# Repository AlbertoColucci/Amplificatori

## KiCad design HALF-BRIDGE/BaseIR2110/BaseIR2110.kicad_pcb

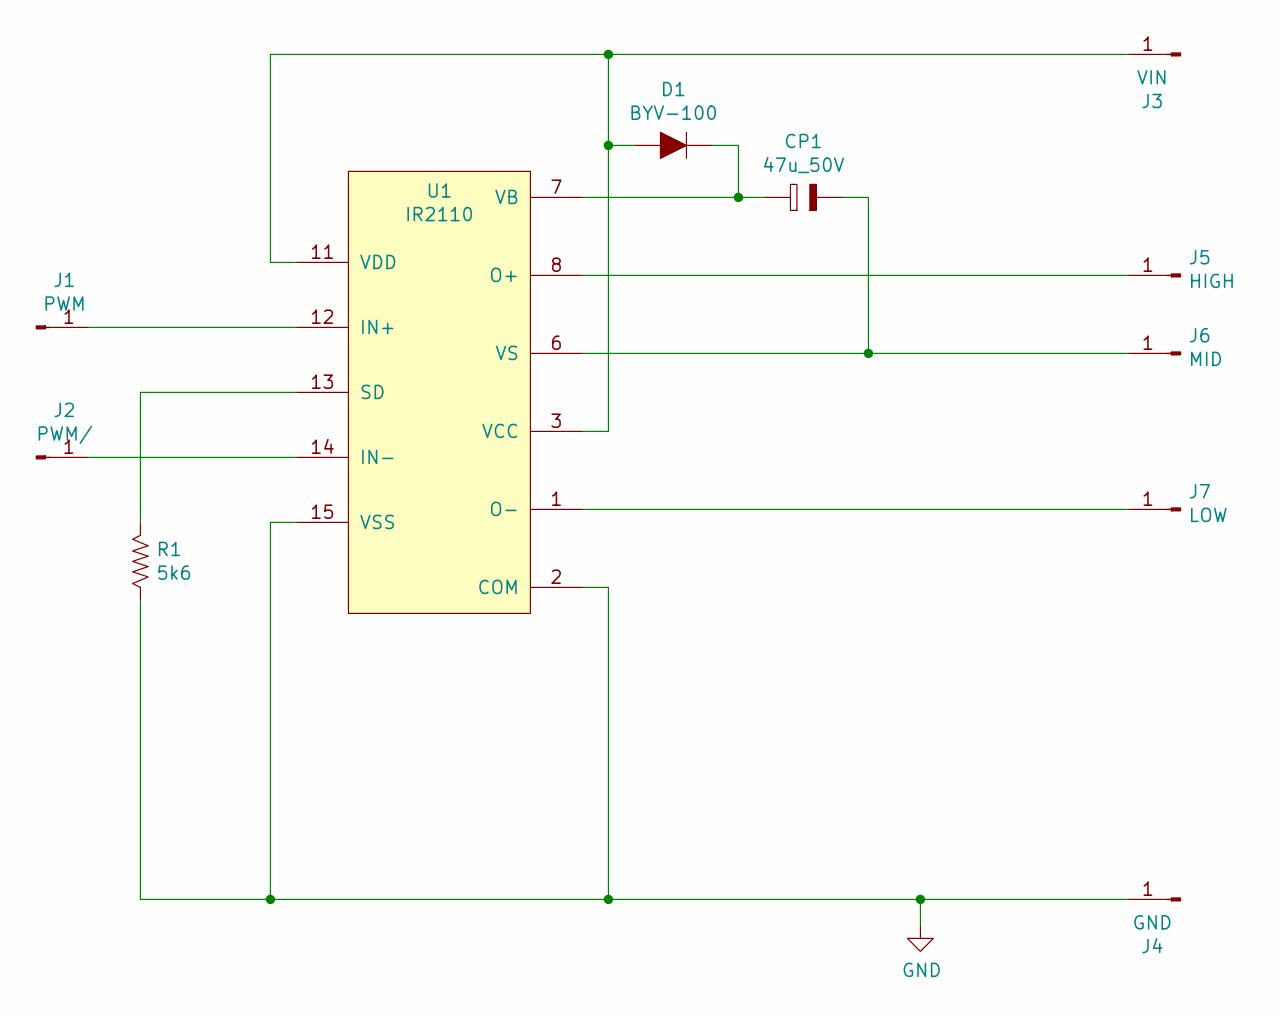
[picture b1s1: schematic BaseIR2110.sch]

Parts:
CP1: 47u_50V; CP_D6.3_P2.54
D1: BYV-100; SOD-64
J1: PWM; 1x1-Pin
J2: PWM/; 1x1-Pin
J3: VIN; 1x1-Pin
J4: GND; 1x1-Pin
J5: HIGH; 1x1-Pin
J6: MID; 1x1-Pin
J7: LOW; 1x1-Pin
R1: 5k6; R_P7.62H
U1: IR2110; SOIC-16W

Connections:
GND: J4.1, R1.2, U1.2 (COM), U1.15 (VSS)
unnamed: CP1.1, J6.1, U1.6 (VS)
unnamed: CP1.2, D1.1 (K), U1.7 (VB)
unnamed: D1.2 (A), J3.1, U1.3 (VCC), U1.11 (VDD)
unnamed: J1.1, U1.12 (IN+)
unnamed: J2.1, U1.14 (IN-)
unnamed: J5.1, U1.8 (O+)
unnamed: J7.1, U1.1 (O-)
unnamed: R1.1, U1.13 (SD)

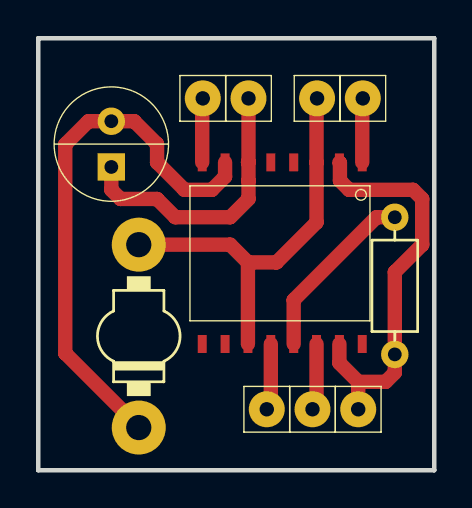
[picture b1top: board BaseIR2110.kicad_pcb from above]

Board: 2 copper layers, 22.0 x 24.0 mm, 11 parts (0 on the bottom side), 9 nets.

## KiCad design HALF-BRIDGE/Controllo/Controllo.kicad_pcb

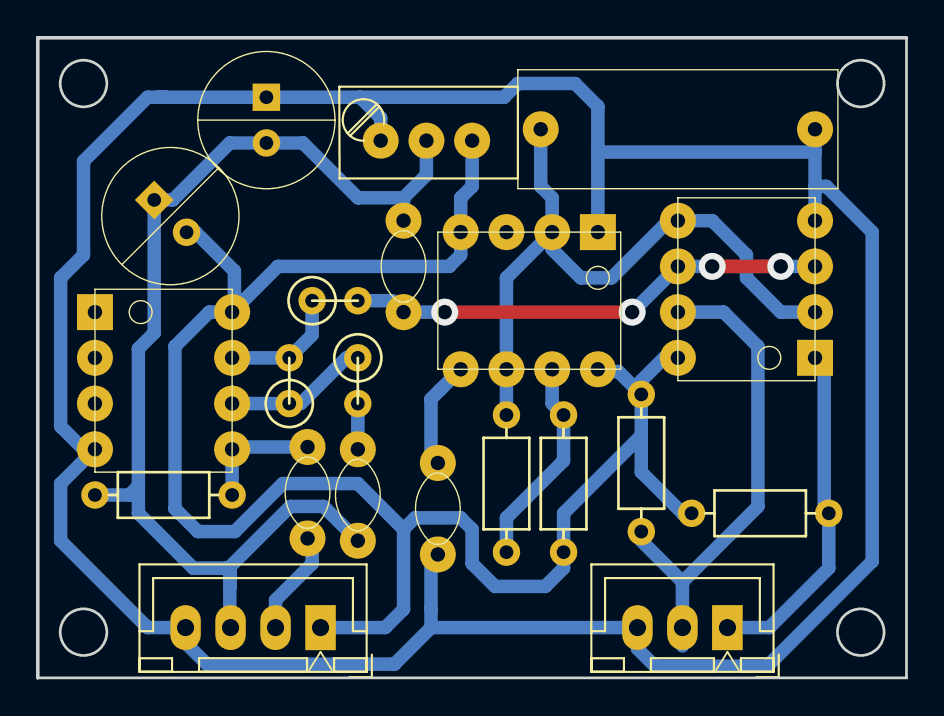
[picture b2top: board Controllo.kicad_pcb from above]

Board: 2 copper layers, 48.3 x 35.6 mm, 21 parts (0 on the bottom side), 14 nets.

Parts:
C1, C3: 1u; C_L5_W2.7_P5.08
C4: 10n; C_L5_W2.7_P5.08
C5: 680p; C_L18_W5.08_P15
C6: 1n; C_L5_W2.7_P5.08
CP1, CP2: 10µ; CP_D7.62_P2.54
J3: PWMOut; 1x03_P2.54
J4: AmpPowerSigIn; 1x04_P2.54
R2: 2.2k; R_P7.62H
R3: 3.3k; R_P2.54V
R4: 36k; R_P2.54V
R5: 680; R_P2.54V
R6: 100; R_P7.62H
R7: 10k; R_P7.62H
R8, R9: 1.5k; R_P7.62H
RV1: 100k; Bourns_3296
U1: LM393; DIP-8
U2: TL072; DIP-8
U3: NE555; DIP-8

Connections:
GND: C5.2, C6.2, CP2.1, J3.3, J4.4, RV1.1, U1.4, U2.4, U3.1
unnamed: C1.1, R2.2, U2.5
unnamed: C1.2, J4.2
unnamed: C3.1, R3.2
unnamed: C3.2, C4.1, CP1.1, CP2.2, J4.3, R2.1, RV1.2
unnamed: C4.2, R5.2, U1.3, U1.6
unnamed: C5.1, R6.2, U1.2, U1.5, U3.2, U3.6
unnamed: C6.1, U3.5
unnamed: J3.1, R8.2, U1.1
unnamed: J3.2, R9.2, U1.7
unnamed: R3.1, R4.1, U2.6
unnamed: R4.2, R5.1, U2.7
unnamed: R6.1, R7.2, U3.7
VCC: CP1.2, J4.1, R7.1, R8.1, R9.1, RV1.3, U1.8, U2.8, U3.4, U3.8

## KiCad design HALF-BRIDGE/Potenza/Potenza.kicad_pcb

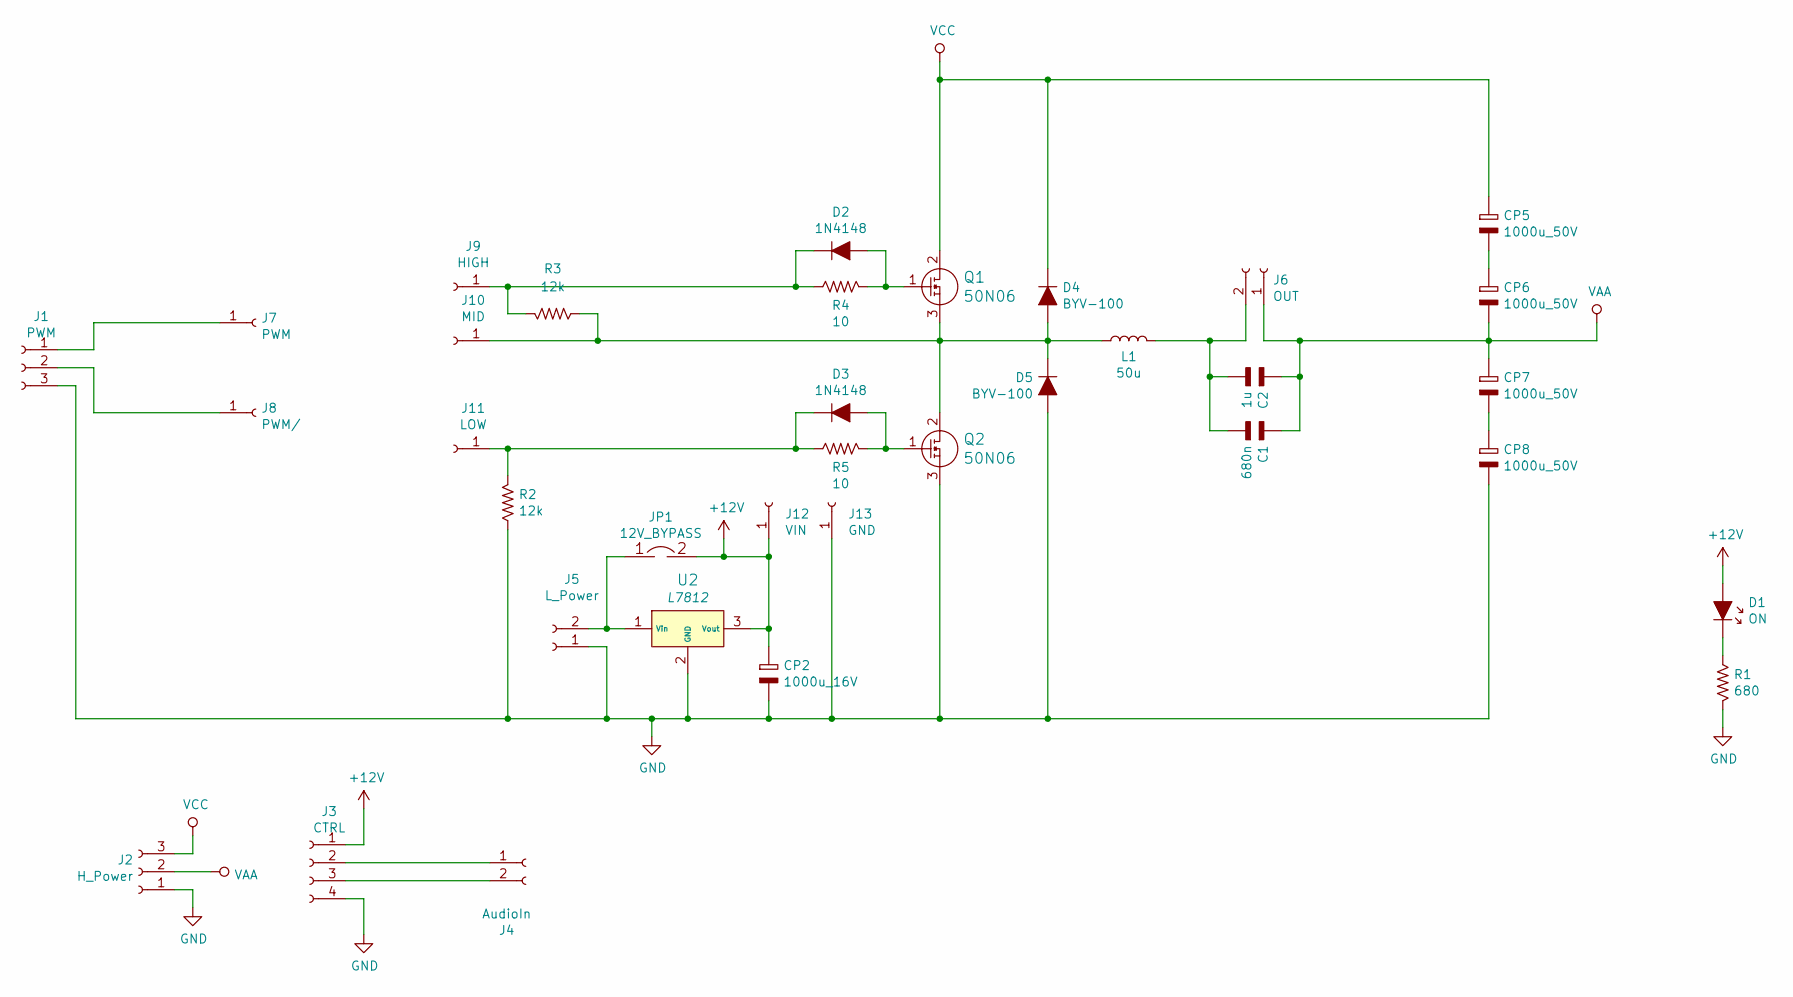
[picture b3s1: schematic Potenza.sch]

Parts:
C1: 680n; C_L23_W6.8_P20
C2: 1u; C_L23_W6.8_P20
CP2: 1000u_16V; CP_D10_P5.08
CP5, CP6, CP7, CP8: 1000u_50V; CP_D13_P5.08
D1: ON; LED_3.0mm
D2, D3: 1N4148; DO-35
D4, D5: BYV-100; SOD-64
J1: PWM; 1x03_P2.54
J2: H_Power; AK300-3
J3: CTRL; 1x04_P2.54
J4: AudioIn; 1x02_P2.54
J5: L_Power; AK300-2
J6: OUT; AK300-2
J7: PWM; 1x1-Pin
J8: PWM/; 1x1-Pin
J9: HIGH; 1x1-Pin
J10: MID; 1x1-Pin
J11: LOW; 1x1-Pin
J12: VIN; 1x1-Pin
J13: GND; 1x1-Pin
JP1: 12V_BYPASS; 1x2-Pin
L1: 50u; T106
Q1, Q2: 50N06; TO-220_3V_FWD
R1: 680; R_P7.62H
R2, R3: 12k; R_P7.62H
R4, R5: 10; R_P7.62H
U2: L7812; TO-220_3H_FWD

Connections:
+12V: CP2.2, D1.1 (A), J3.1, J12.1, JP1.2, U2.3 (Vout)
GND: CP2.1, CP8.1, D5.2 (A), J1.3, J2.1, J3.4, J5.1, J13.1, Q2.3 (S), R1.2, R2.1, U2.2 (GND)
unnamed: C1.2, C2.2, J6.2, L1.2
unnamed: CP5.1, CP6.2
unnamed: CP7.1, CP8.2
unnamed: D1.2 (K), R1.1
unnamed: D2.1 (K), J9.1, R3.2, R4.1
unnamed: D2.2 (A), Q1.1 (G), R4.2
unnamed: D3.1 (K), J11.1, R2.2, R5.1
unnamed: D3.2 (A), Q2.1 (G), R5.2
unnamed: D4.2 (A), D5.1 (K), J10.1, L1.1, Q1.3 (S), Q2.2 (D), R3.1
unnamed: J1.1, J7.1
unnamed: J1.2, J8.1
unnamed: J3.2, J4.1
unnamed: J3.3, J4.2
unnamed: J5.2, JP1.1, U2.1 (Vin)
VAA: C1.1, C2.1, CP6.1, CP7.2, J2.2, J6.1
VCC: CP5.2, D4.1 (K), J2.3, Q1.2 (D)

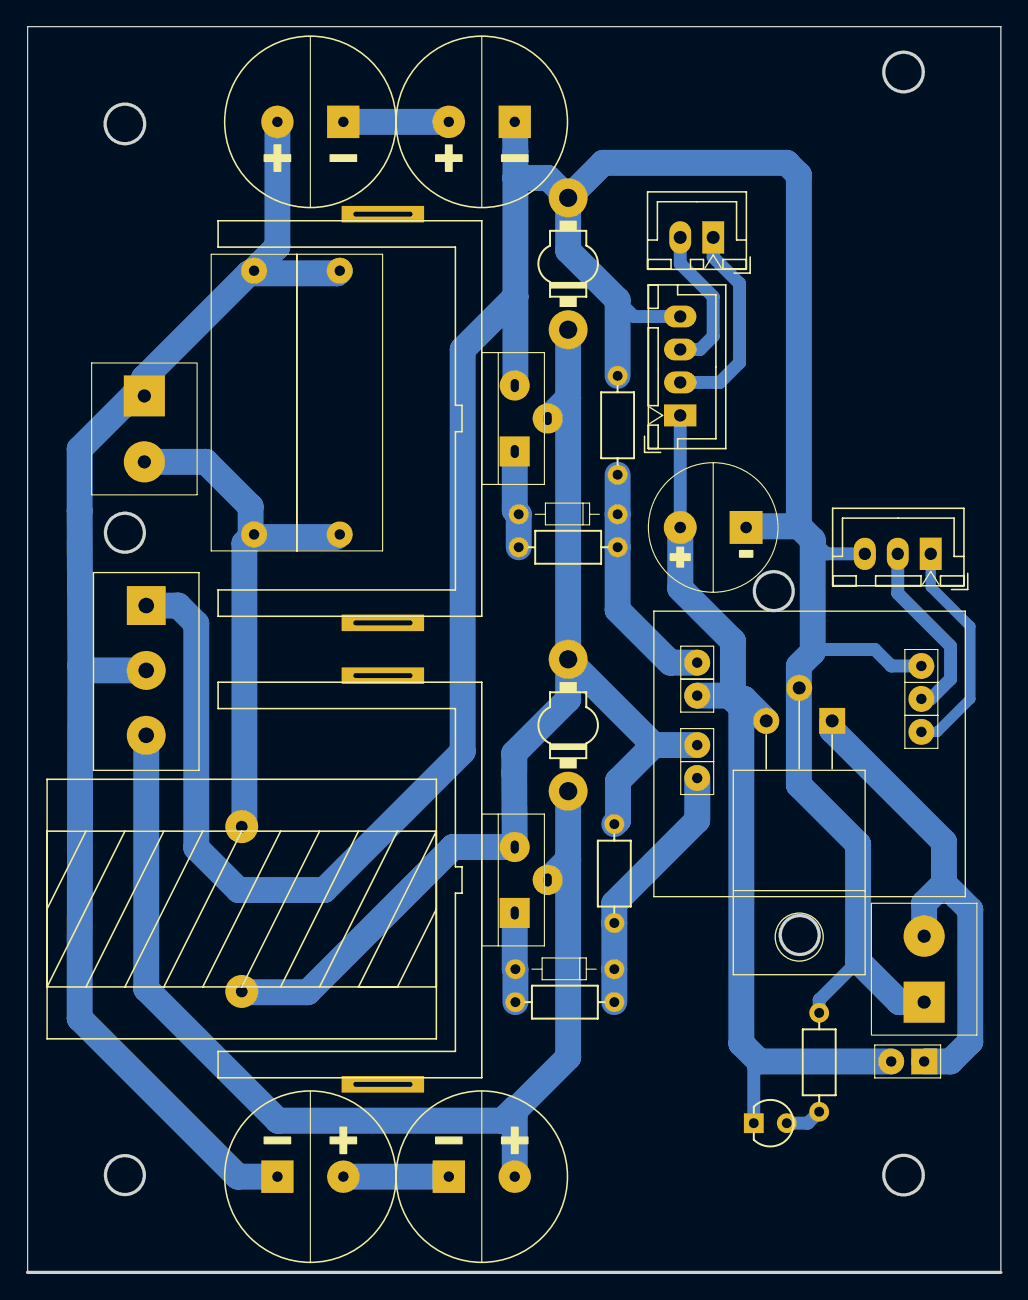
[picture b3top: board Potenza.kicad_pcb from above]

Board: 2 copper layers, 75.0 x 96.0 mm, 35 parts (0 on the bottom side), 18 nets.

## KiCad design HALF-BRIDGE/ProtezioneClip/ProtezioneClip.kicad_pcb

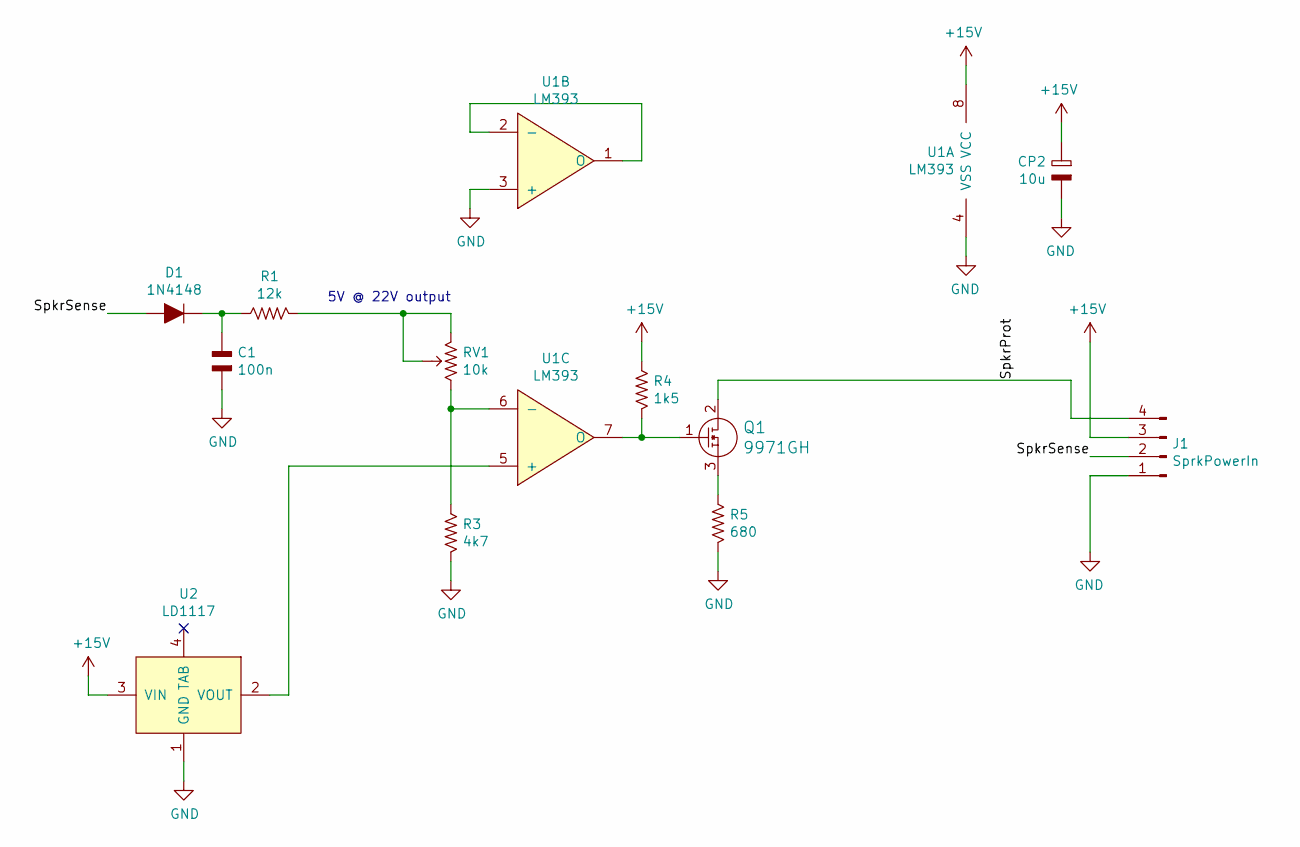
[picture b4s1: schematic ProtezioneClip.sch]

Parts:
C1: 100n; C_L5_W2.7_P5.08
CP2: 10u; CP_D5_P2.54
D1: 1N4148; DO-35
J1: SprkPowerIn; 1x04_P2.54
Q1: 9971GH; TO-252_3_Tab2
R1: 12k; R_P2.54V
R3: 4k7; R_P7.62H
R4: 1k5; R_P2.54V
R5: 680; R_P7.62H
RV1: 10k; Bourns_3296
U1: LM393; SOIC-8
U2: LD1117; SOT-223

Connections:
+15V: CP2.2, J1.3, R4.1, U1.8 (VCC), U2.3 (VIN)
/SpkrProt: J1.4, Q1.2 (D)
/SpkrSense: D1.2 (A), J1.2
GND: C1.1, CP2.1, J1.1, R3.2, R5.2, U1.3 (+), U1.4 (VSS), U2.1 (GND)
unnamed: C1.2, D1.1 (K), R1.1
unnamed: Q1.1 (G), R4.2, U1.7 (O)
unnamed: Q1.3 (S), R5.1
unnamed: R1.2, RV1.2, RV1.3
unnamed: R3.1, RV1.1, U1.6 (-)
unnamed: U1.1 (O), U1.2 (-)
unnamed: U1.5 (+), U2.2 (VOUT)

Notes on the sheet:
5V @ 22V output

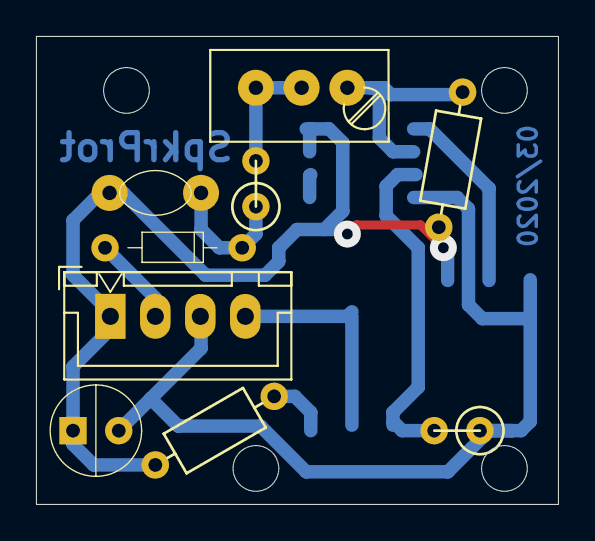
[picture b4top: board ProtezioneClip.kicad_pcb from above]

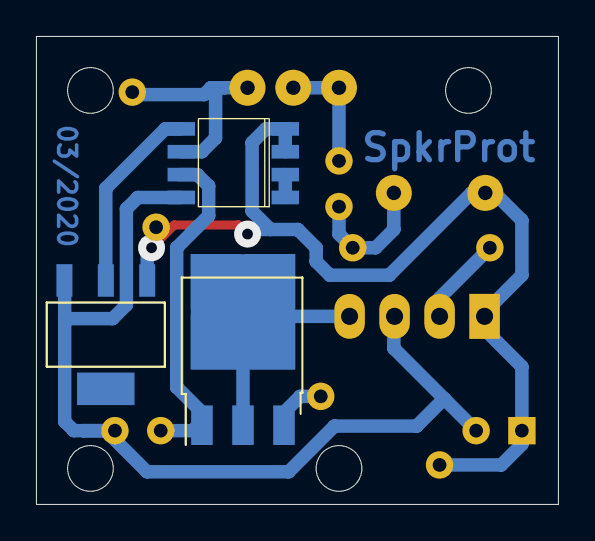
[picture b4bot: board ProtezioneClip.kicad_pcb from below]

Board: 2 copper layers, 29.0 x 26.0 mm, 12 parts (3 on the bottom side), 11 nets.

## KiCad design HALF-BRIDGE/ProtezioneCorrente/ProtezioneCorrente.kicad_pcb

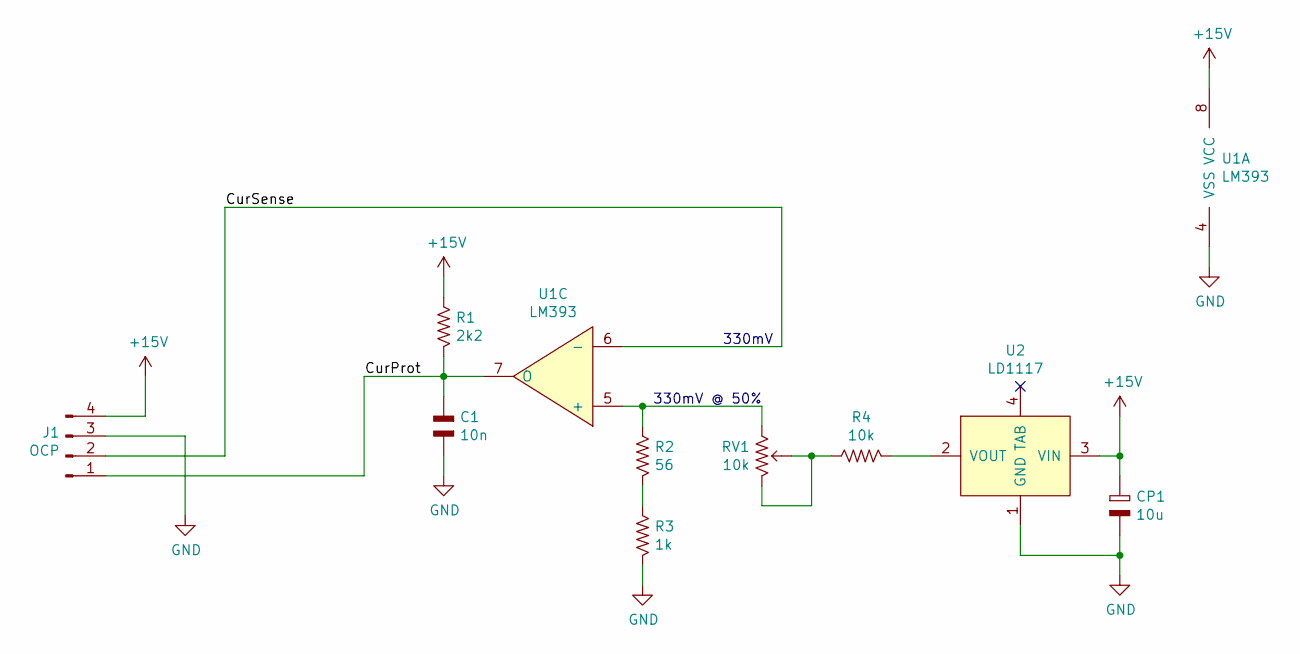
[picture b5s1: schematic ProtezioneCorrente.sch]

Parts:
C1: 10n; C_L5_W2.7_P5.08
CP1: 10u; CP_D5_P2.54
J1: OCP; 1x04_P2.54
R1: 2k2; R_P7.62H
R2: 56; R_P2.54V
R3: 1k; R_P7.62H
R4: 10k; R_P2.54V
RV1: 10k; Bourns_3296
U1: LM393; SOIC-8
U2: LD1117; SOT-223

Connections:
+15V: CP1.2, J1.4, R1.1, U1.8 (VCC), U2.3 (VIN)
/CurProt: C1.1, J1.1, R1.2, U1.7 (O)
/CurSense: J1.2, U1.6 (-)
GND: C1.2, CP1.1, J1.3, R3.2, U1.4 (VSS), U2.1 (GND)
unnamed: R2.1, RV1.1, U1.5 (+)
unnamed: R2.2, R3.1
unnamed: R4.1, RV1.2, RV1.3
unnamed: R4.2, U2.2 (VOUT)

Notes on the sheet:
330mV
330mV @ 50%

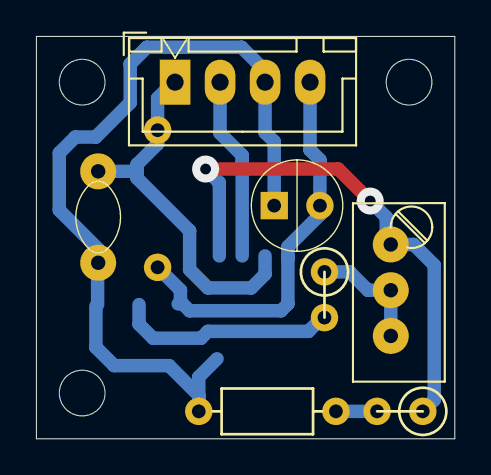
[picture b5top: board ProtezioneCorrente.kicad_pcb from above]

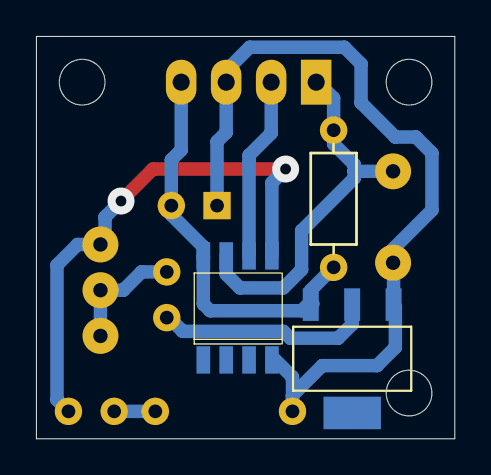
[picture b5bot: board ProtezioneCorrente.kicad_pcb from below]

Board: 2 copper layers, 23.2 x 22.4 mm, 10 parts (3 on the bottom side), 8 nets.

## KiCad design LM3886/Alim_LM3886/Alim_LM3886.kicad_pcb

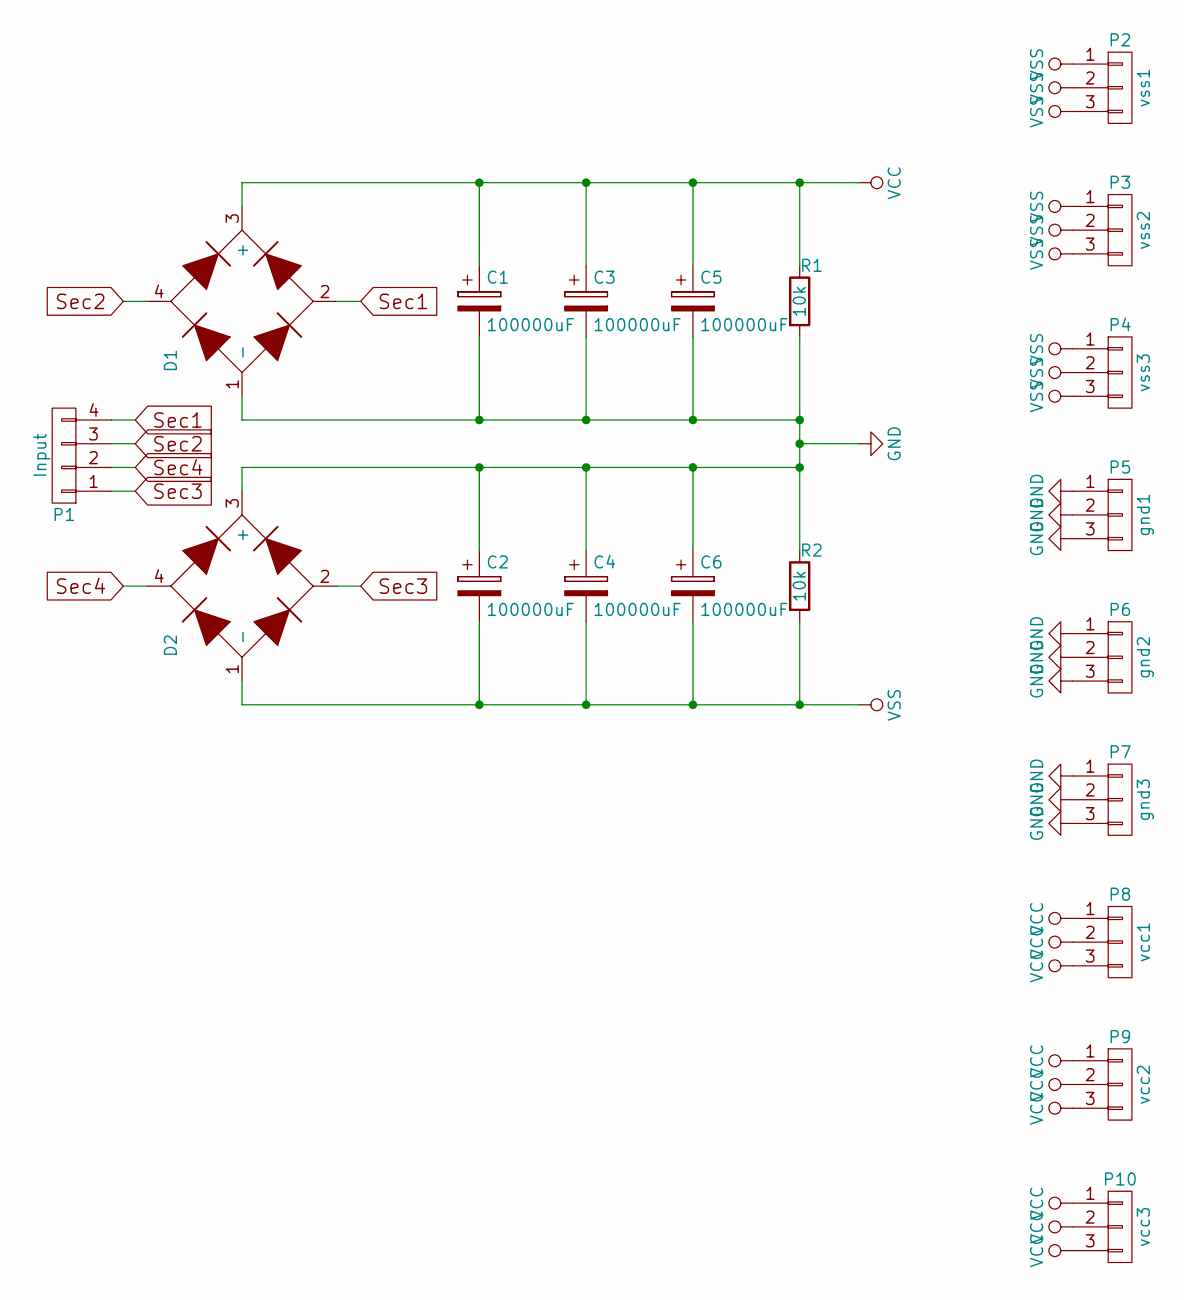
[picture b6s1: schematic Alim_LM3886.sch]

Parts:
C1, C2, C3, C4, C5, C6: 100000uF; CP_Radial_D30.0mm_P10.00mm_SnapIn
D1, D2: Diode_Bridge; KBPC3510
P1: Input; AK300-4
P2: vss1; AK300-3
P3: vss2; AK300-3
P4: vss3; AK300-3
P5: gnd1; AK300-3
P6: gnd2; AK300-3
P7: gnd3; AK300-3
P8: vcc1; AK300-3
P9: vcc2; AK300-3
P10: vcc3; AK300-3
R1, R2: 10k; Res_Orizz_10mm

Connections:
GND: C1.2, C2.1, C3.2, C4.1, C5.2, C6.1, D1.1 (-), D2.3 (+), P5.1, P5.2, P5.3, P6.1, P6.2, P6.3, P7.1, P7.2, P7.3, R1.2, R2.1
Sec1: D1.2, P1.4
Sec2: D1.4, P1.3
Sec3: D2.2, P1.1
Sec4: D2.4, P1.2
VCC: C1.1, C3.1, C5.1, D1.3 (+), P8.1, P8.2, P8.3, P9.1, P9.2, P9.3, P10.1, P10.2, P10.3, R1.1
VSS: C2.2, C4.2, C6.2, D2.1 (-), P2.1, P2.2, P2.3, P3.1, P3.2, P3.3, P4.1, P4.2, P4.3, R2.2

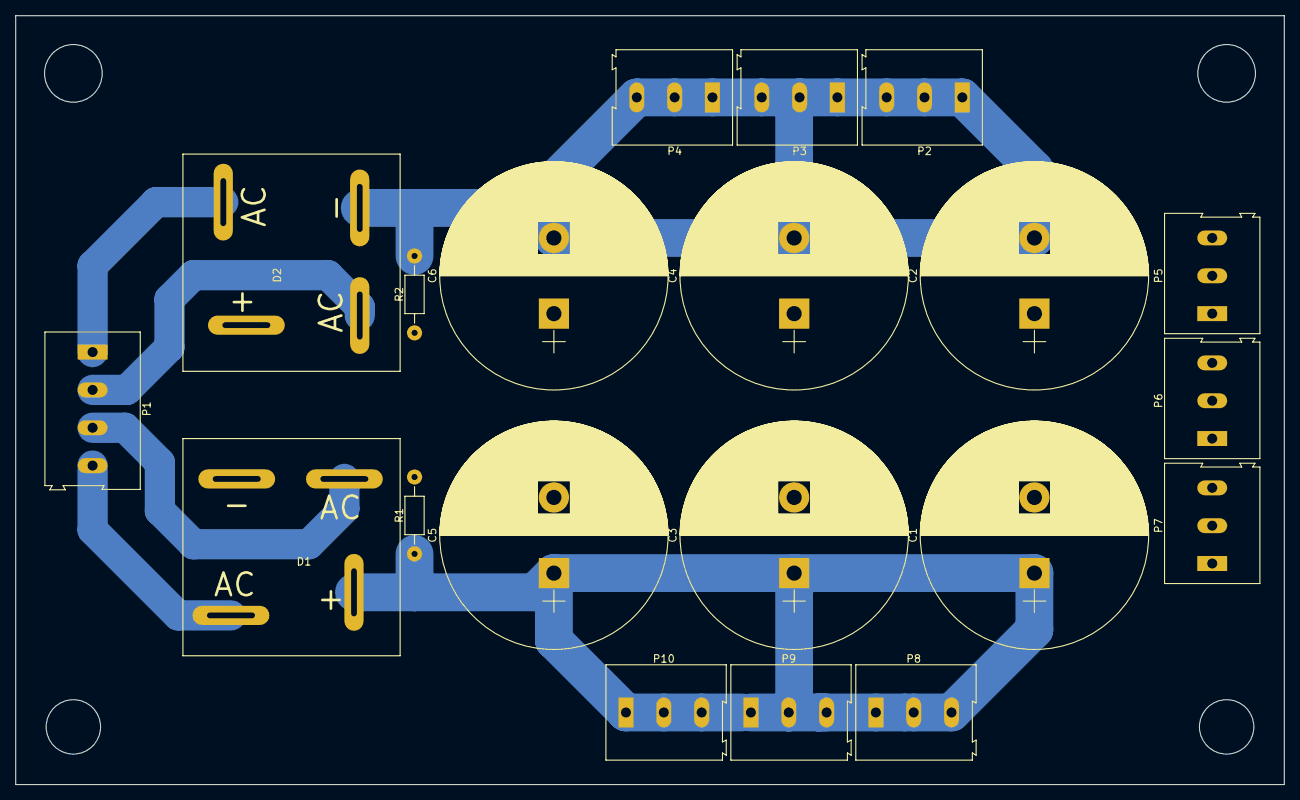
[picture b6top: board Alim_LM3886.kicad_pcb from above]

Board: 2 copper layers, 167.6 x 101.6 mm, 20 parts (0 on the bottom side), 7 nets.

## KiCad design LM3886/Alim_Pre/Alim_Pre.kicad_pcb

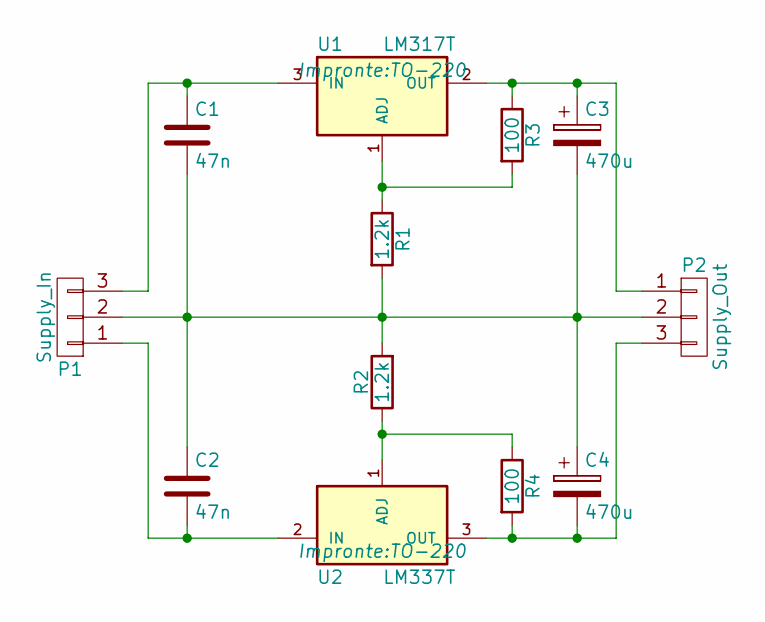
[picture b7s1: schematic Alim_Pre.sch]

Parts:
C1, C2: 47n; Cap_7x2.5
C3, C4: 470u; Cap_10x13
P1: Supply_In; AK300-3
P2: Supply_Out; AK300-3
R1, R2: 1.2k; Res_Orizz_10mm
R3, R4: 100; Res_Orizz_10mm
U1: LM317T; TO-220
U2: LM337T; TO-220

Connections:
unnamed: C1.1, P1.3, U1.3 (IN)
unnamed: C1.2, C2.1, C3.2, C4.1, P1.2, P2.2, R1.2, R2.2
unnamed: C2.2, P1.1, U2.2 (IN)
unnamed: C3.1, P2.1, R3.1, U1.2 (OUT)
unnamed: C4.2, P2.3, R4.2, U2.3 (OUT)
unnamed: R1.1, R3.2, U1.1 (ADJ)
unnamed: R2.1, R4.1, U2.1 (ADJ)

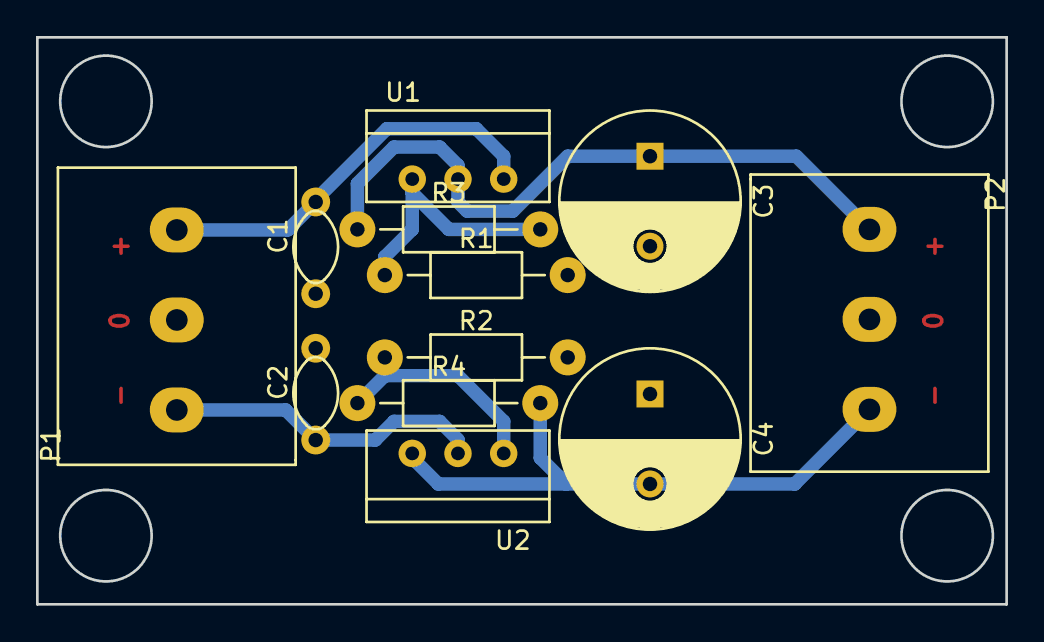
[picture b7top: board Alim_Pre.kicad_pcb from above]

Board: 2 copper layers, 53.8 x 31.5 mm, 12 parts (0 on the bottom side), 7 nets.

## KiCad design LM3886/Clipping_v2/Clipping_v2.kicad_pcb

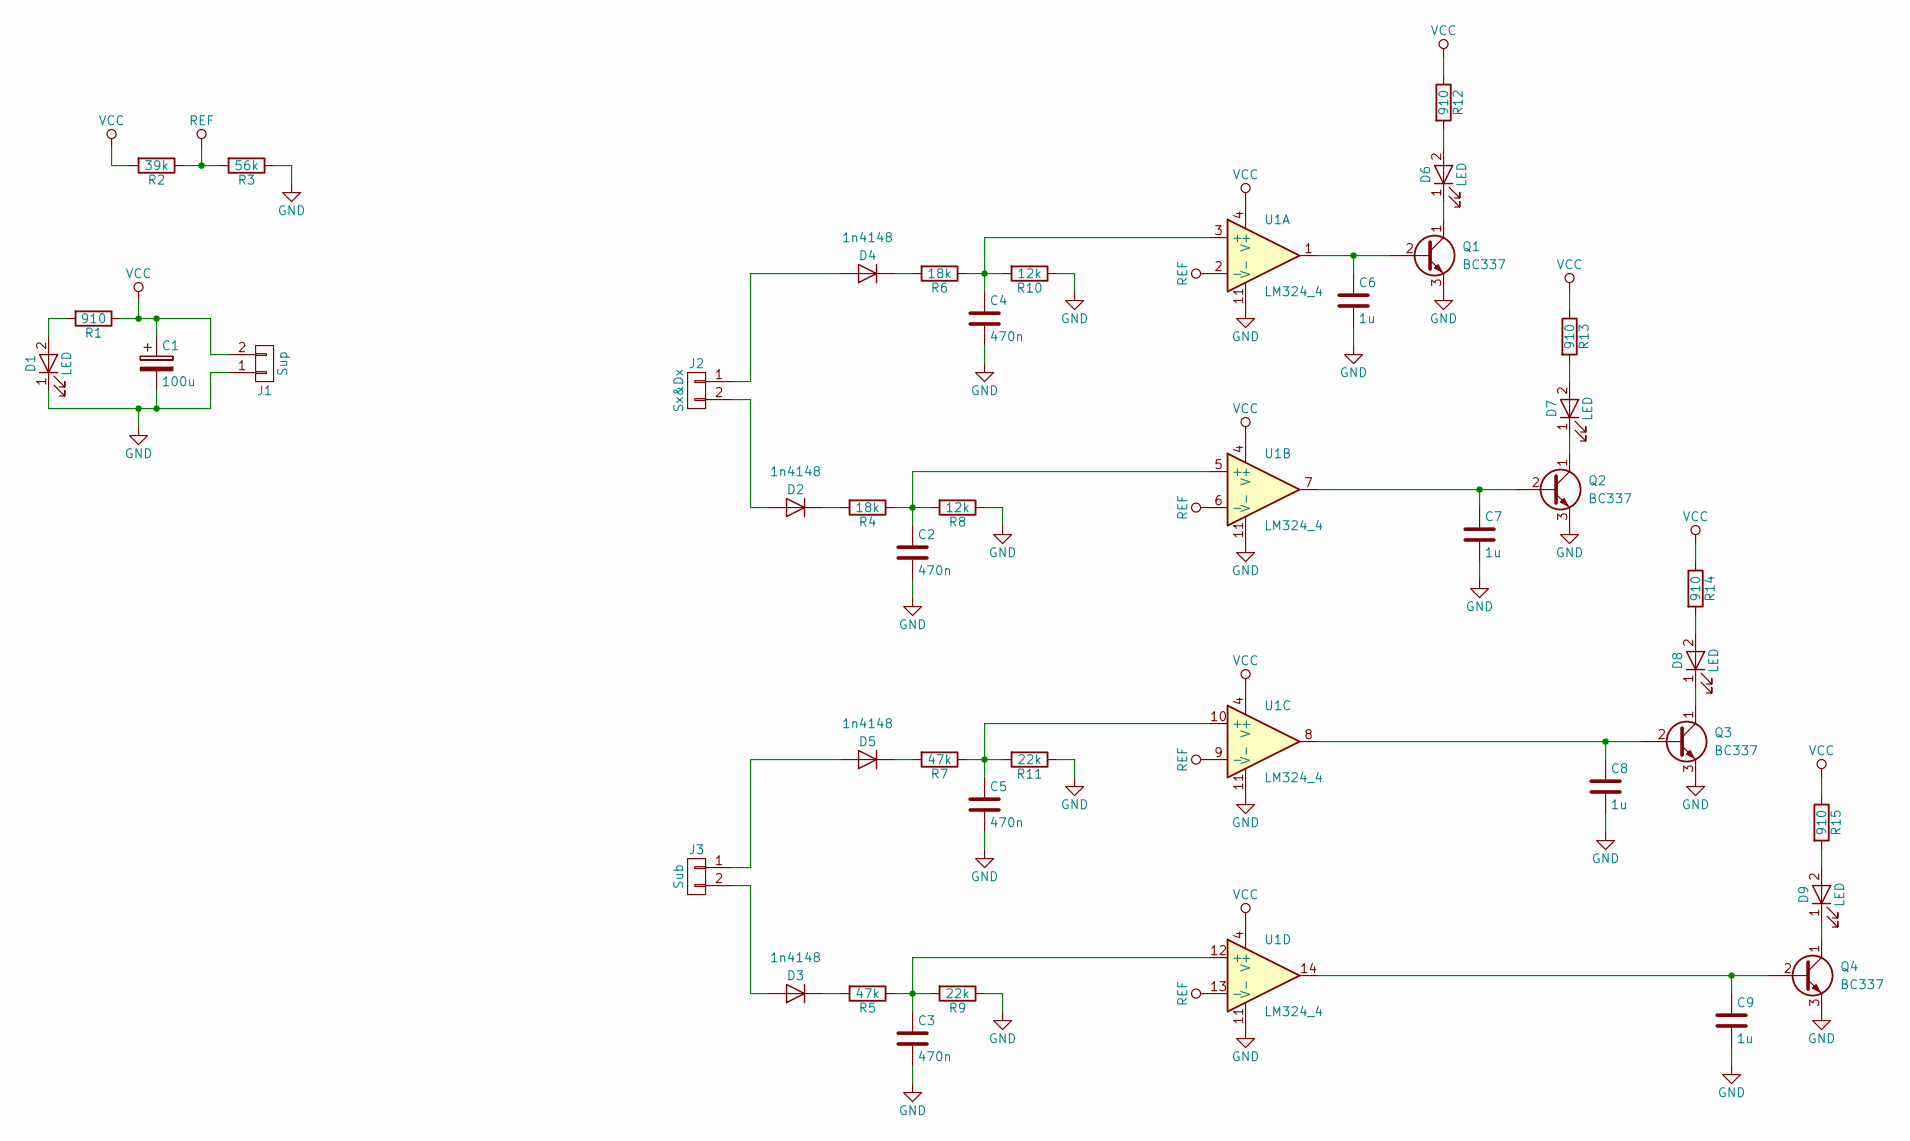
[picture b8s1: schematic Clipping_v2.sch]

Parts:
C1: 100u; Cap_10
C2, C3, C4, C5: 470n; Cap_5x2.7
C6, C7, C8, C9: 1u; Cap_5x2.7
D1, D6, D7, D8, D9: LED; LED_D3.0mm
D2, D3, D4, D5: 1n4148; DO-35
J1: Sup; AK300-2
J2: Sx&Dx; AK300-2
J3: Sub; AK300-2
Q1, Q2, Q3, Q4: BC337; TO-92
R1, R12, R13, R14, R15: 910; Res_Orizz_7mm
R2: 39k; Res_Orizz_7mm
R3: 56k; Res_Orizz_7mm
R4, R6: 18k; Res_Orizz_7mm
R5, R7: 47k; Res_Orizz_7mm
R8, R10: 12k; Res_Orizz_7mm
R9, R11: 22k; Res_Orizz_7mm
U1: LM324_4; DIP-14

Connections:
GND: C1.2, C2.2, C3.2, C4.2, C5.2, C6.2, C7.2, C8.2, C9.2, D1.1 (K), J1.1, Q1.3 (E), Q2.3 (E), Q3.3 (E), Q4.3 (E), R3.1, R8.1, R9.1, R10.1, R11.1, U1.11 (V-)
unnamed: C2.1, R4.1, R8.2, U1.5 (+)
unnamed: C3.1, R5.1, R9.2, U1.12 (+)
unnamed: C4.1, R6.1, R10.2, U1.3 (+)
unnamed: C5.1, R7.1, R11.2, U1.10 (+)
unnamed: C6.1, Q1.2 (B), U1.1
unnamed: C7.1, Q2.2 (B), U1.7
unnamed: C8.1, Q3.2 (B), U1.8
unnamed: C9.1, Q4.2 (B), U1.14
unnamed: D1.2 (A), R1.2
unnamed: D2.1 (K), R4.2
unnamed: D2.2 (A), J2.2
unnamed: D3.1 (K), R5.2
unnamed: D3.2 (A), J3.2
unnamed: D4.1 (K), R6.2
unnamed: D4.2 (A), J2.1
unnamed: D5.1 (K), R7.2
unnamed: D5.2 (A), J3.1
unnamed: D6.1 (K), Q1.1 (C)
unnamed: D6.2 (A), R12.2
unnamed: D7.1 (K), Q2.1 (C)
unnamed: D7.2 (A), R13.2
unnamed: D8.1 (K), Q3.1 (C)
unnamed: D8.2 (A), R14.2
unnamed: D9.1 (K), Q4.1 (C)
unnamed: D9.2 (A), R15.2
REF: R2.1, R3.2, U1.2 (-), U1.6 (-), U1.9 (-), U1.13 (-)
VCC: C1.1, J1.2, R1.1, R2.2, R12.1, R13.1, R14.1, R15.1, U1.4 (V+)

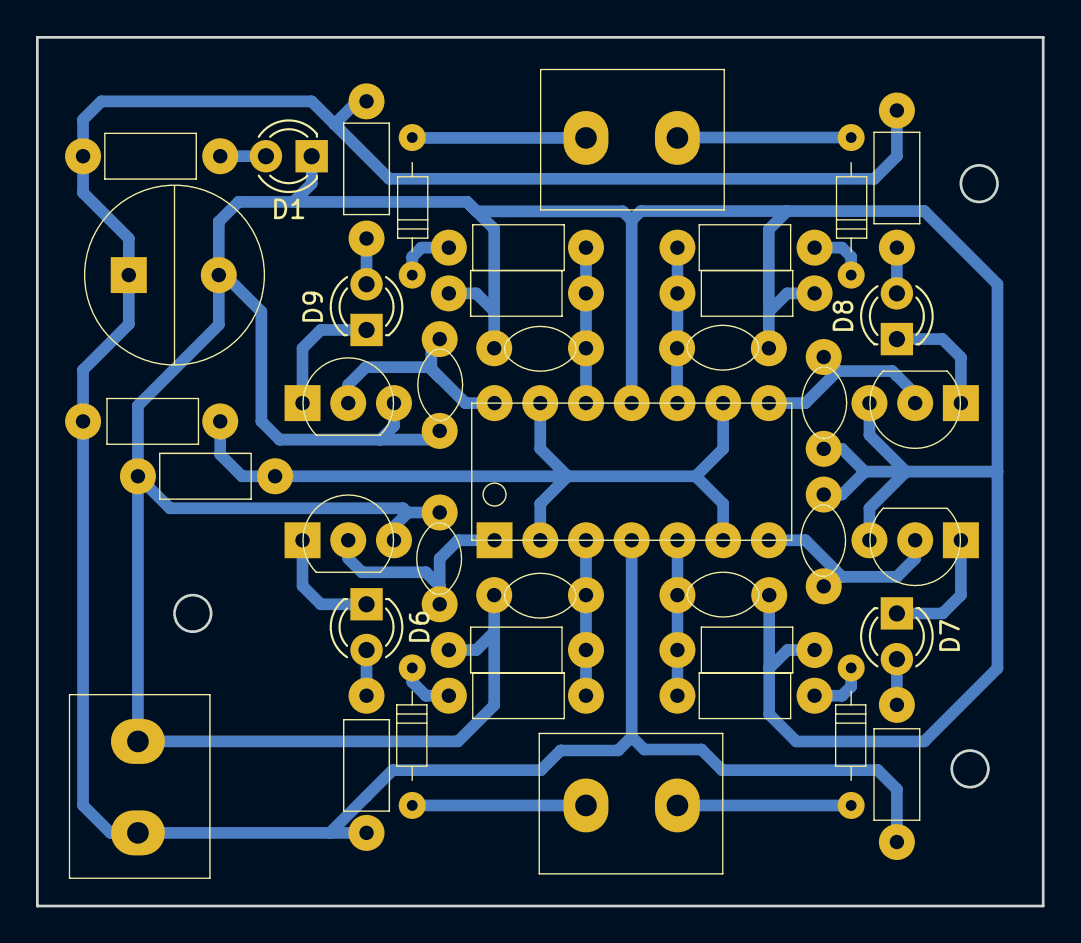
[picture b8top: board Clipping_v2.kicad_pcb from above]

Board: 2 copper layers, 55.9 x 48.3 mm, 41 parts (0 on the bottom side), 28 nets.
